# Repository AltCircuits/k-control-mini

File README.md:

# K-Control Mini

K-Control Mini for the Ksoloti Core.

Features:
- MIDI In/Out via 3.5mm TRS Jacks (Type A)
- Stereo Audio In/Out via 3.5mm TRS Jacks
- Headphone Out via 3.5mm TRS Jack
- 3x 10k Pots
- 1x 10k Pot with Center Detent
- RGB LED
- 2x Push Button/LED Combo (Blue and Orange)

---
Ksoloti is based on the Axoloti by Johannes Taelman (johannes.taelman@gmail.com)

Template by [@sebiik](https://github.com/sebiik)

[Axoloti website](http://www.axoloti.com/)

[Ksoloti website](https://ksoloti.github.io/index.html)

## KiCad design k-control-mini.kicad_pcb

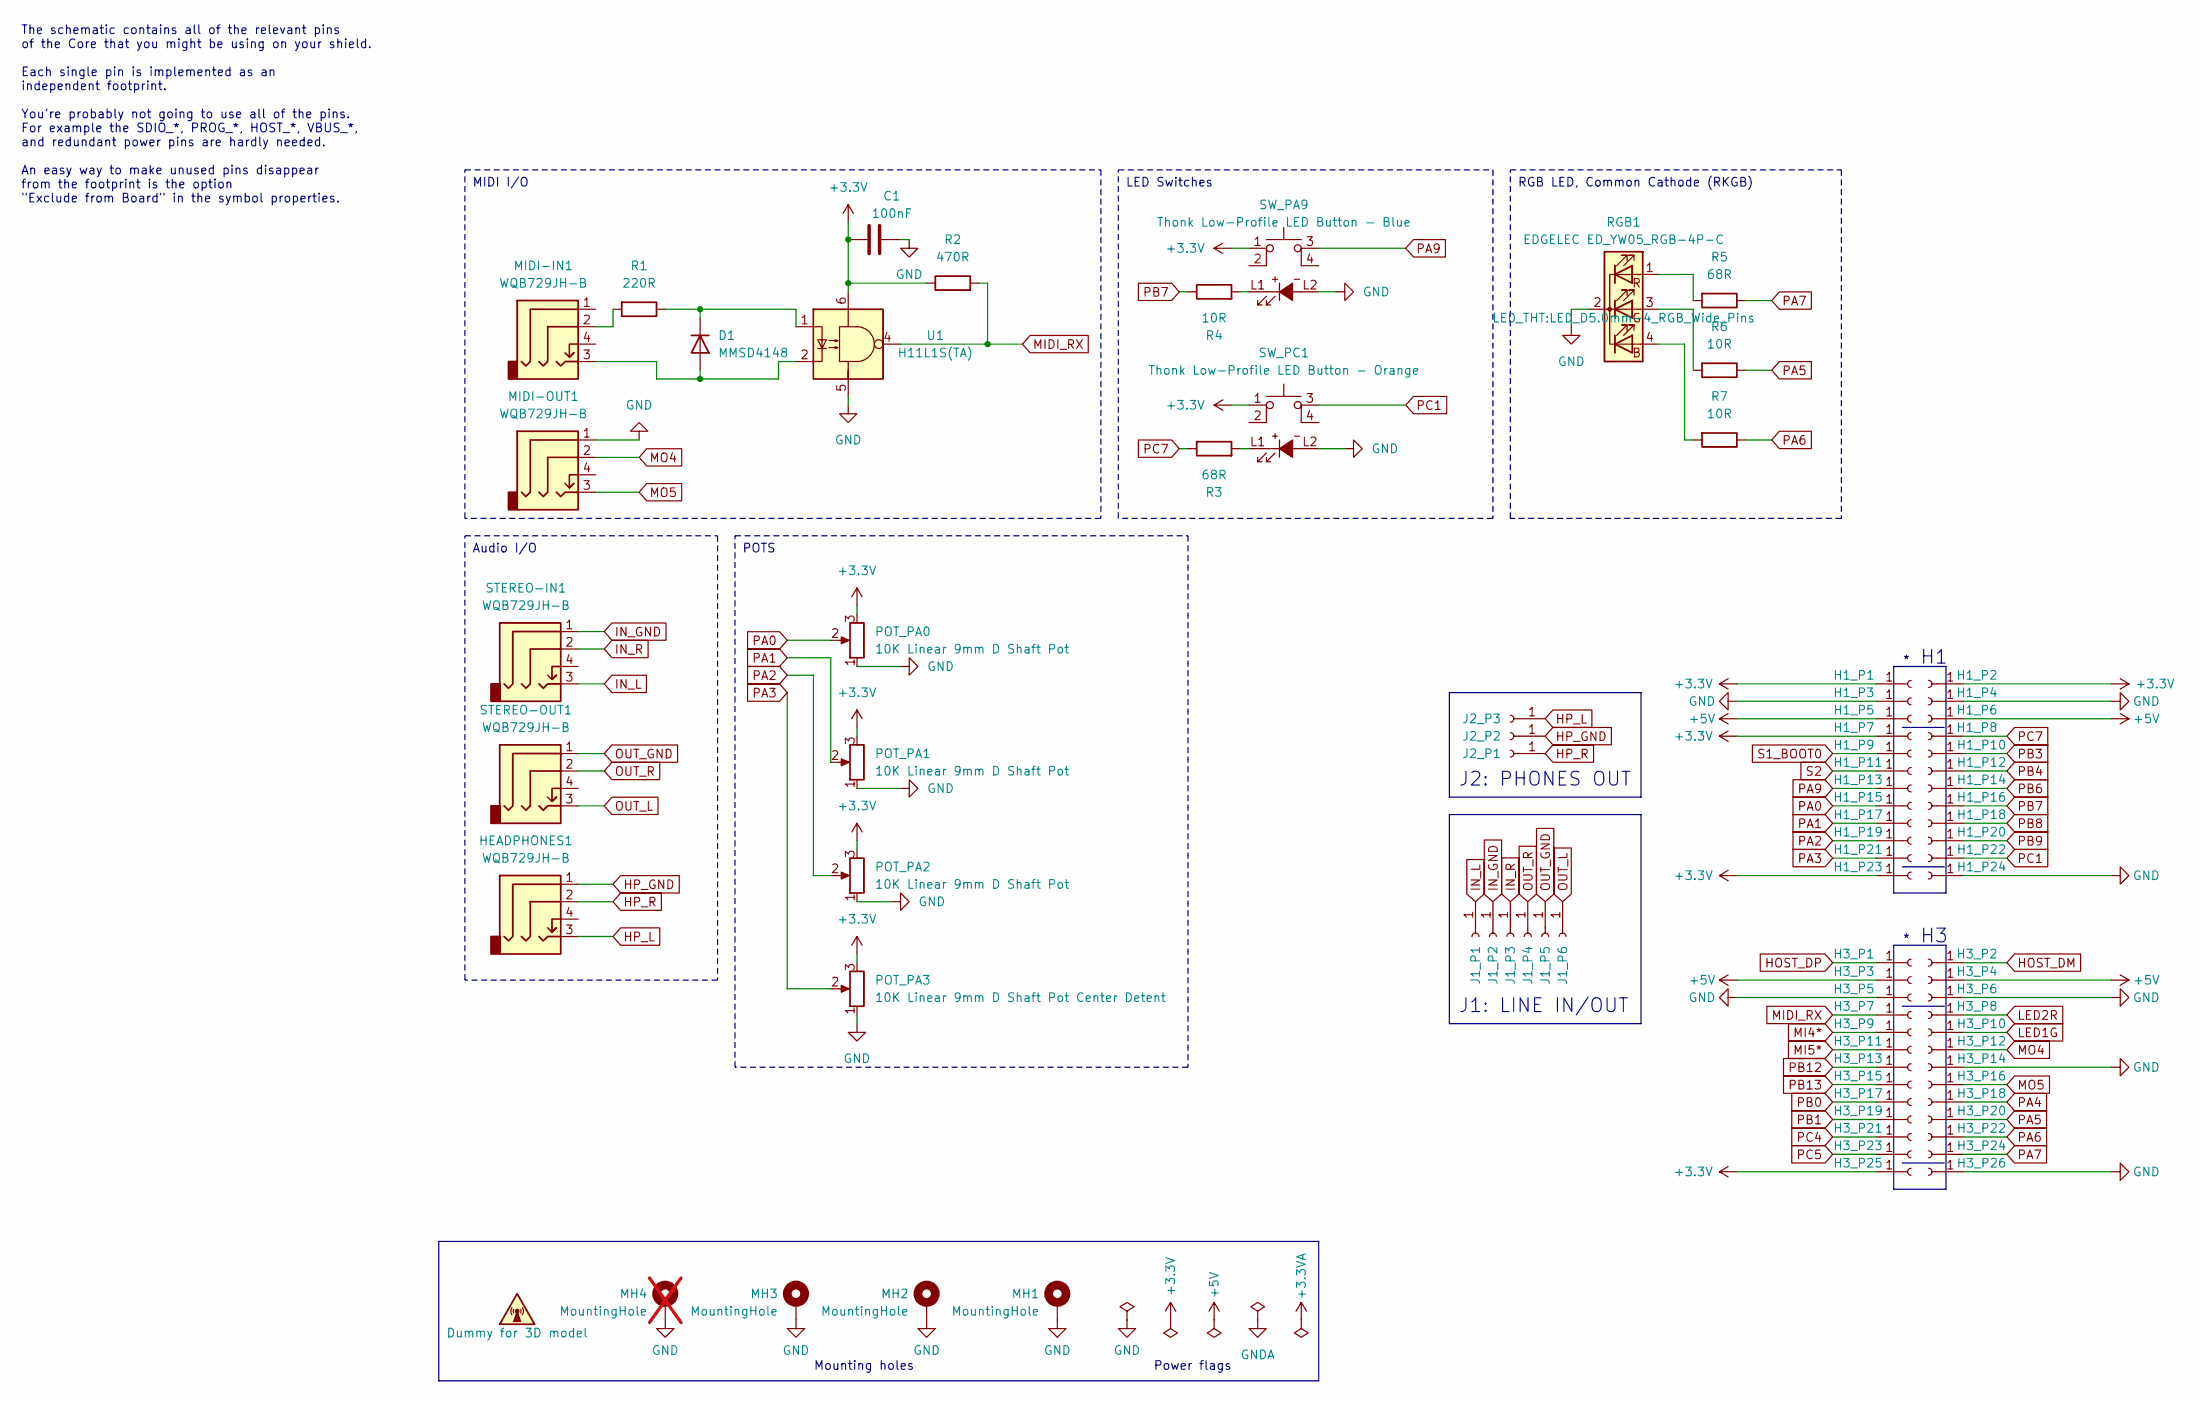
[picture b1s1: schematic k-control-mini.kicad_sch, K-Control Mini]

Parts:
C1: 100nF; C_0603_1608Metric
D1: MMSD4148; D_SOD-123
DUMMY1: Dummy for 3D model
H1_P1: +3.3V; PinSocket_1x01_P2.54mm_Vertical_smcrt_sqr
H1_P2, H1_P7, H1_P23, H3_P25: +3.3V; PinSocket_1x01_P2.54mm_Vertical_smcrt_round
H1_P3, H1_P4, H1_P24, H3_P5, H3_P6, H3_P14, H3_P26: GND; PinSocket_1x01_P2.54mm_Vertical_smcrt_round
H1_P5, H1_P6, H3_P3, H3_P4: +5V; PinSocket_1x01_P2.54mm_Vertical_smcrt_round
H1_P8: PC7; PinSocket_1x01_P2.54mm_Vertical_smcrt_round
H1_P9: S1_BOOT0; PinSocket_1x01_P2.54mm_Vertical_smcrt_round
H1_P10: PB3; PinSocket_1x01_P2.54mm_Vertical_smcrt_round
H1_P11: S2; PinSocket_1x01_P2.54mm_Vertical_smcrt_round
H1_P12: PB4; PinSocket_1x01_P2.54mm_Vertical_smcrt_round
H1_P13: PA9; PinSocket_1x01_P2.54mm_Vertical_smcrt_round
H1_P14: PB6; PinSocket_1x01_P2.54mm_Vertical_smcrt_round
H1_P15: PA0; PinSocket_1x01_P2.54mm_Vertical_smcrt_round
H1_P16: PB7; PinSocket_1x01_P2.54mm_Vertical_smcrt_round
H1_P17: PA1; PinSocket_1x01_P2.54mm_Vertical_smcrt_round
H1_P18: PB8; PinSocket_1x01_P2.54mm_Vertical_smcrt_round
H1_P19: PA2; PinSocket_1x01_P2.54mm_Vertical_smcrt_round
H1_P20: PB9; PinSocket_1x01_P2.54mm_Vertical_smcrt_round
H1_P21: PA3; PinSocket_1x01_P2.54mm_Vertical_smcrt_round
H1_P22: PC1; PinSocket_1x01_P2.54mm_Vertical_smcrt_round
H3_P1: HOST_DP; PinSocket_1x01_P2.54mm_Vertical_smcrt_sqr
H3_P2: HOST_DM; PinSocket_1x01_P2.54mm_Vertical_smcrt_round
H3_P7: MIDI_RX; PinSocket_1x01_P2.54mm_Vertical_smcrt_round
H3_P8: LED2R; PinSocket_1x01_P2.54mm_Vertical_smcrt_round
H3_P9: MI4; PinSocket_1x01_P2.54mm_Vertical_smcrt_round
H3_P10: LED1G; PinSocket_1x01_P2.54mm_Vertical_smcrt_round
H3_P11: MI5; PinSocket_1x01_P2.54mm_Vertical_smcrt_round
H3_P12: MO4; PinSocket_1x01_P2.54mm_Vertical_smcrt_round
H3_P13: PB12; PinSocket_1x01_P2.54mm_Vertical_smcrt_round
H3_P15: PB13; PinSocket_1x01_P2.54mm_Vertical_smcrt_round
H3_P16: MO5; PinSocket_1x01_P2.54mm_Vertical_smcrt_round
H3_P17: PB0; PinSocket_1x01_P2.54mm_Vertical_smcrt_round
H3_P18: PA4; PinSocket_1x01_P2.54mm_Vertical_smcrt_round
H3_P19: PB1; PinSocket_1x01_P2.54mm_Vertical_smcrt_round
H3_P20: PA5; PinSocket_1x01_P2.54mm_Vertical_smcrt_round
H3_P21: PC4; PinSocket_1x01_P2.54mm_Vertical_smcrt_round
H3_P22: PA6; PinSocket_1x01_P2.54mm_Vertical_smcrt_round
H3_P23: PC5; PinSocket_1x01_P2.54mm_Vertical_smcrt_round
H3_P24: PA7; PinSocket_1x01_P2.54mm_Vertical_smcrt_round
HEADPHONES1: WQB729JH-B; 729JH-B
J1_P1: IN_L; PinSocket_1x01_P2.54mm_Vertical_smcrt_sqr
J1_P2: IN_GND; PinSocket_1x01_P2.54mm_Vertical_smcrt_round
J1_P3: IN_R; PinSocket_1x01_P2.54mm_Vertical_smcrt_round
J1_P4: OUT_R; PinSocket_1x01_P2.54mm_Vertical_smcrt_round
J1_P5: OUT_GND; PinSocket_1x01_P2.54mm_Vertical_smcrt_round
J1_P6: OUT_L; PinSocket_1x01_P2.54mm_Vertical_smcrt_round
J2_P1: HP_R; PinSocket_1x01_P2.54mm_Vertical_smcrt_sqr
J2_P2: HP_GND; PinSocket_1x01_P2.54mm_Vertical_smcrt_round
J2_P3: HP_L; PinSocket_1x01_P2.54mm_Vertical_smcrt_round
MH1, MH2, MH3: MountingHole; MountingHole_3.2mm_M3_Pad_Via_tight
MH4: MountingHole; MountingHole_3.2mm_M3_Pad_Via_tight; not fitted
MIDI-IN1: WQB729JH-B; 729JH-B
MIDI-OUT1: WQB729JH-B; 729JH-B
POT_PA0, POT_PA1, POT_PA2: 10K Linear 9mm D Shaft Pot; Potentiometer_Alpha_RD901F-40-00D_Single_Vertical
POT_PA3: 10K Linear 9mm D Shaft Pot Center Detent; Potentiometer_Alpha_RD901F-40-00D_Single_Vertical
R1: 220R; R_0603_1608Metric
R2: 470R; R_0603_1608Metric
R3, R5: 68R; R_0603_1608Metric
R4, R6, R7: 10R; R_0603_1608Metric
RGB1: EDGELEC ‎ED_YW05_RGB-4P-C; LED_D5.0mm-4_RGB_Wide_Pins
STEREO-IN1: WQB729JH-B; 729JH-B
STEREO-OUT1: WQB729JH-B; 729JH-B
SW_PA9: Thonk Low-Profile LED Button - Blue; SW_Push_LED_Thonk
SW_PC1: Thonk Low-Profile LED Button - Orange; SW_Push_LED_Thonk
U1: H11L1S(TA); H11L1STA_EVE

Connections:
+3.3V: C1.1, H1_P1.1, H1_P2.1, H1_P7.1, H1_P23.1, H3_P25.1, POT_PA0.3, POT_PA1.3, POT_PA2.3, POT_PA3.3, R2.1, SW_PA9.1, SW_PC1.1, U1.6
+5V: H1_P5.1, H1_P6.1, H3_P3.1, H3_P4.1
GND: C1.2, H1_P3.1, H1_P4.1, H1_P24.1, H3_P5.1, H3_P6.1, H3_P14.1, H3_P26.1, MH1.1, MH2.1, MH3.1, MH4.1, MIDI-OUT1.1, POT_PA0.1, POT_PA1.1, POT_PA2.1, POT_PA3.1, RGB1.2 (K), SW_PA9.L2, SW_PC1.L2, U1.5
HOST_DM: H3_P2.1
HOST_DP: H3_P1.1
HP_GND: HEADPHONES1.1, J2_P2.1
HP_L: HEADPHONES1.3, J2_P3.1
HP_R: HEADPHONES1.2, J2_P1.1
IN_GND: J1_P2.1, STEREO-IN1.1
IN_L: J1_P1.1, STEREO-IN1.3
IN_R: J1_P3.1, STEREO-IN1.2
LED1G: H3_P10.1
LED2R: H3_P8.1
MI4*: H3_P9.1
MI5*: H3_P11.1
MIDI_RX: H3_P7.1, R2.2, U1.4
MO4: H3_P12.1, MIDI-OUT1.2
MO5: H3_P16.1, MIDI-OUT1.3
unnamed: D1.2 (A), MIDI-IN1.3, U1.2
unnamed: D1.1 (K), R1.1, U1.1
unnamed: MIDI-IN1.2, R1.2
unnamed: R3.2, SW_PC1.L1
unnamed: R4.2, SW_PA9.L1
unnamed: R7.2, RGB1.4 (BA)
unnamed: R6.2, RGB1.3 (GA)
unnamed: R5.2, RGB1.1 (RA)
OUT_GND: J1_P5.1, STEREO-OUT1.1
OUT_L: J1_P6.1, STEREO-OUT1.3
OUT_R: J1_P4.1, STEREO-OUT1.2
PA0: H1_P15.1, POT_PA0.2
PA1: H1_P17.1, POT_PA1.2
PA2: H1_P19.1, POT_PA2.2
PA3: H1_P21.1, POT_PA3.2
PA4: H3_P18.1
PA5: H3_P20.1, R6.1
PA6: H3_P22.1, R7.1
PA7: H3_P24.1, R5.1
PA9: H1_P13.1, SW_PA9.3
PB0: H3_P17.1
PB1: H3_P19.1
PB3: H1_P10.1
PB4: H1_P12.1
PB6: H1_P14.1
PB7: H1_P16.1, R4.1
PB8: H1_P18.1
PB9: H1_P20.1
PB12: H3_P13.1
PB13: H3_P15.1
PC1: H1_P22.1, SW_PC1.3
PC4: H3_P21.1
PC5: H3_P23.1
PC7: H1_P8.1, R3.1
S1_BOOT0: H1_P9.1
S2: H1_P11.1

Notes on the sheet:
RGB LED, Common Cathode (RKGB)
MIDI I/O
POTS
Audio I/O
LED Switches
J2: PHONES OUT
The schematic contains all of the relevant pins of the Core that you might be using on your shield. Each single pin is implemented as an independent footprint. You're probably not going to use all of the pins. For example the SDIO_*, PROG_*, HOST_*, VBUS_*, and redundant power pins are hardly neede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
Mounting holes
Power flags
J1: LINE IN/OUT

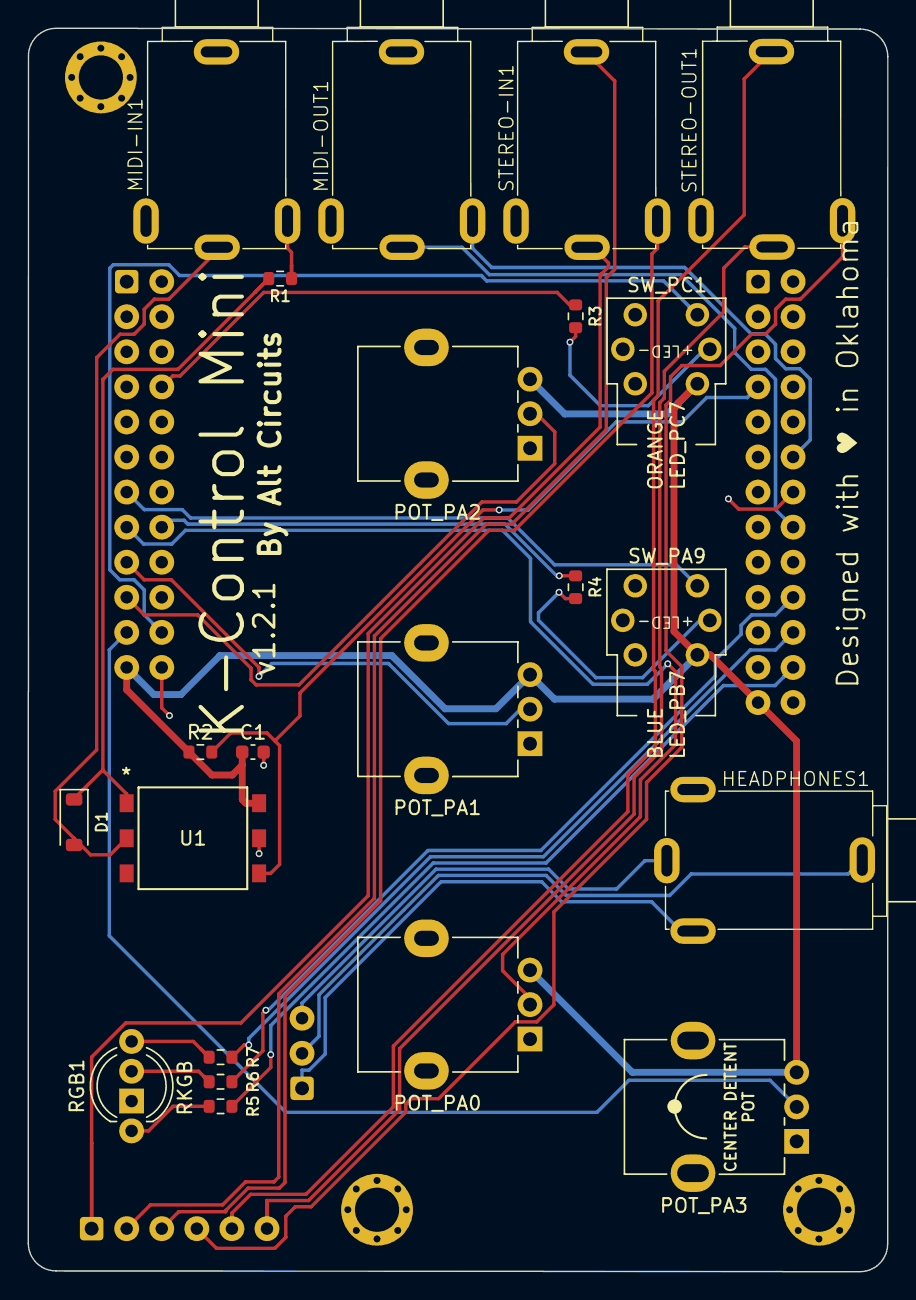
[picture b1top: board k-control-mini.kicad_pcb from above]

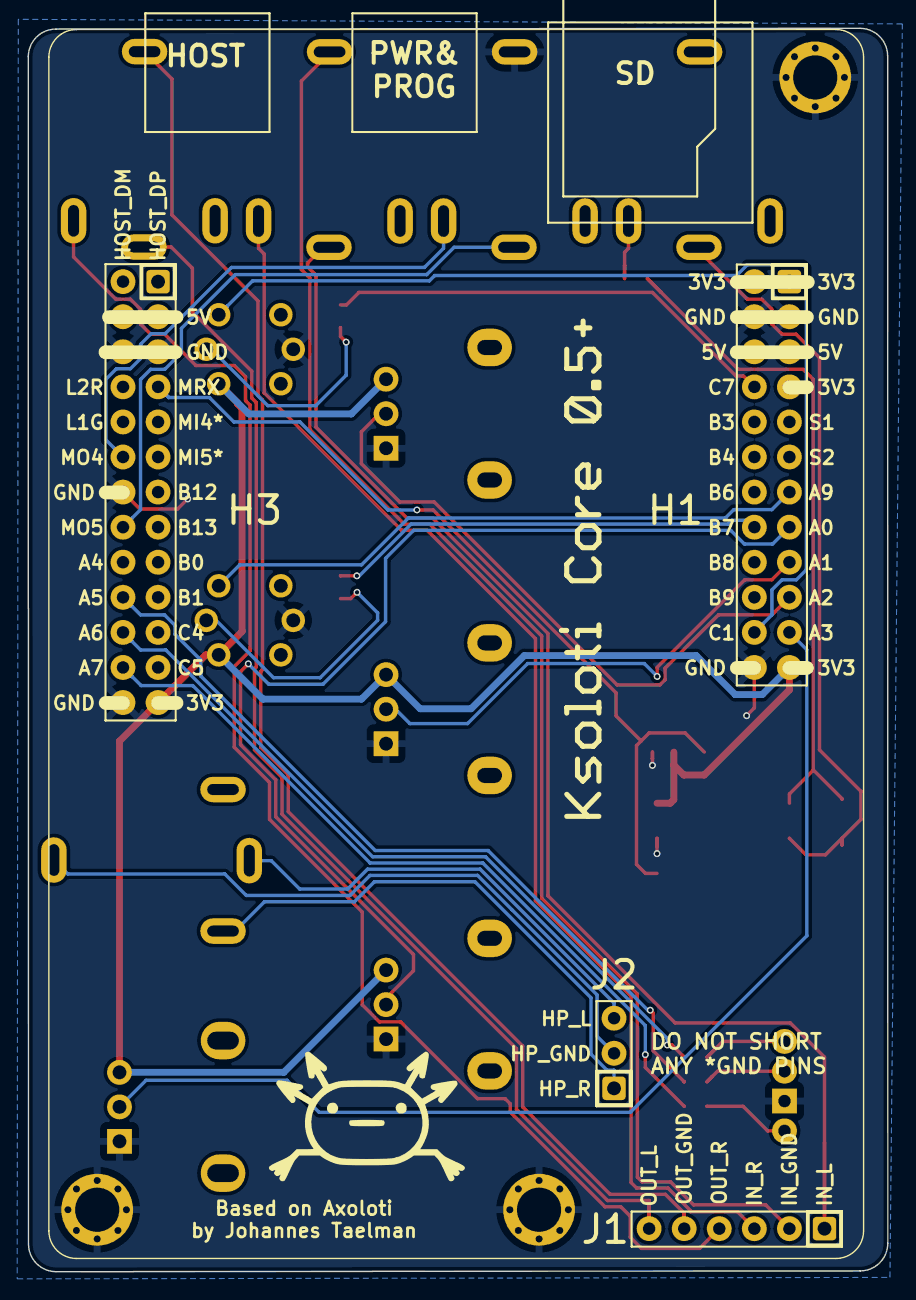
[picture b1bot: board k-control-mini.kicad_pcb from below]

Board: 2 copper layers, 62.2 x 90.0 mm, 86 parts (64 on the bottom side), 34 nets.

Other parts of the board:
G513513: LOGO

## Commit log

2023-12-17 initial
2023-12-20 thonk blue jacks
2023-12-20 footprint arangements
2023-12-23 updated footprint locations for thonk jacks
2023-12-28 added thonk jacks model
2024-01-03 updated testing patch for new I/O
2024-01-03 rearranged board so audio jacks are on same side as USB
2024-01-03 fixed traces and silk screen
2024-01-03 updated test patch to reflect new design
2024-01-07 updated silkscreen and test patch
2024-01-19 typo fix
